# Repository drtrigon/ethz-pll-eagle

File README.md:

## Projekte
### Blattdurchmesser

https://gitlab.ethz.ch/PLL/Blattdurchmesser

https://github.com/drtrigon/ethz-pll-eagle/tree/result/pcb

## Setup

I would like to use features like CI (continous integration) keep a copy/mirror on e.g. github and more.

ETHZ GitLab could (and may be already does) support such features but I do not understand how this works.

Maintaining a copy/mirror (more precise: with 2 remotes overloaded origin) on GitHub also allows
to use GitLab and GitHub together and by that all the nice featurs on GitHub.
See also; https://steveperkins.com/migrating-projects-from-github-to-gitlab/

"Option 2: Overload Origin with Both Remotes (needs one single pull/push only)"; in order to clone
and set this repo up use:
```
$ git clone https://gitlab.ethz.ch/PLL/eagle.git
$ cd eagle
$ git remote set-url --add origin https://github.com/drtrigon/ethz-pll-eagle.git
```
you can check the settings with:
```
$ git remote -v
origin  https://gitlab.ethz.ch/PLL/eagle.git (fetch)
origin  https://gitlab.ethz.ch/PLL/eagle.git (push)
origin  https://github.com/drtrigon/ethz-pll-eagle.git (push)
```

### Enable EDRC.ME for a Repository (for Eagle)
http://www.edrc.me/docs/

### Further Info
https://github.com/drtrigon/eagle

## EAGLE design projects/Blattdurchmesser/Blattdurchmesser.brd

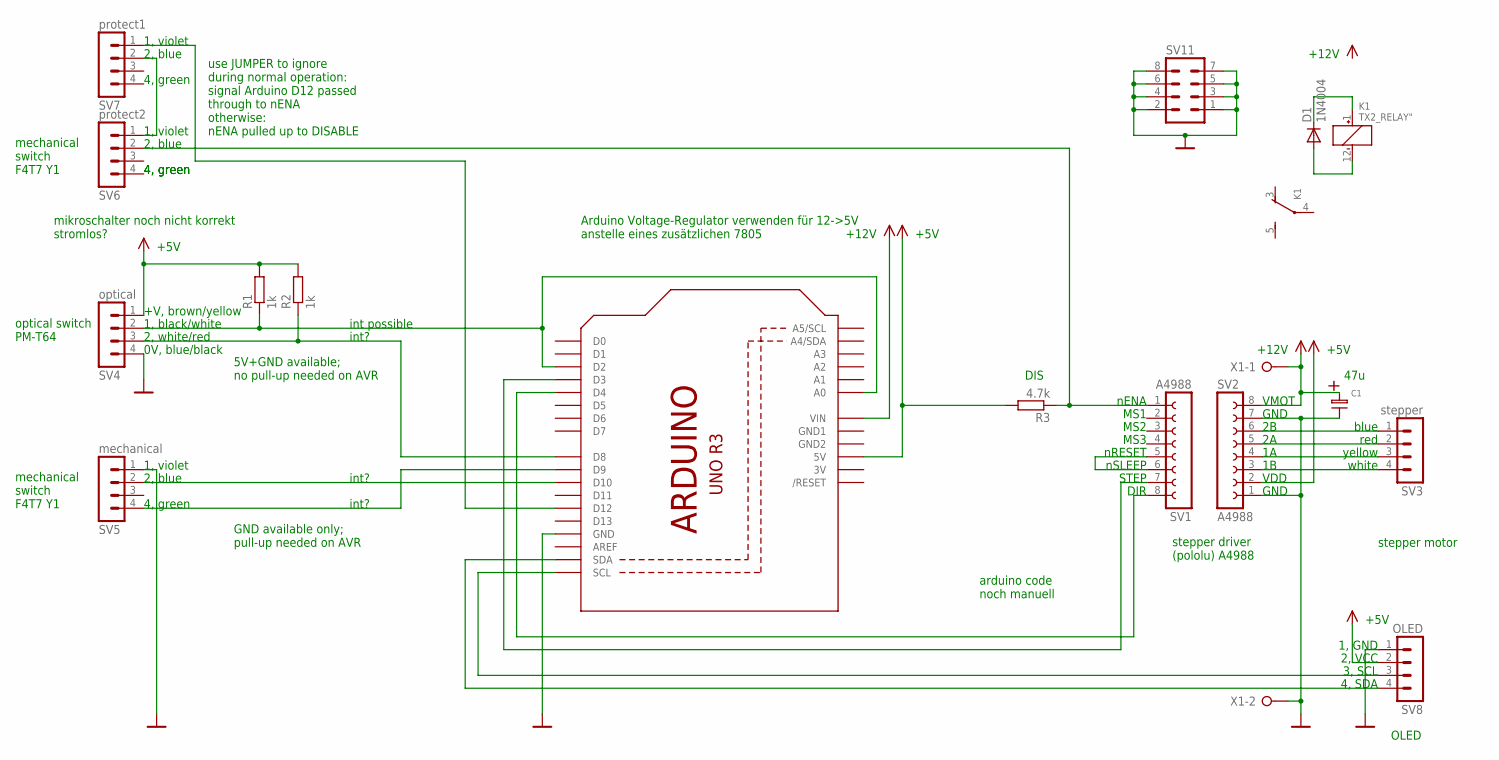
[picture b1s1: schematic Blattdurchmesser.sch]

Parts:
C1: R_ELKO_8.1; R_ELK_8.1
D1: 1N4004; DO41-10
K1: TX2_RELAY"; TX2
Q1: ARDUINOR3-NOIOREF-NOTEXT; ARDUINOR3-NOTEXT-NOIOREF
R1, R2: 1k; 0207/10
R3: 4.7k; 0207/10
SV1, SV2: A4988; FE08
SV3: stepper; MA04-1
SV4: optical; MA04-1
SV5: mechanical; MA04-1
SV6: protect2; MA04-1
SV7: protect1; MA04-1
SV8: OLED; MA04-1
SV11: MA04-2
X1: W237-02P; W237-132

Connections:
3V: Q1.3V
+5V: Q1.5V, R1.2, R2.2, R3.2, SV2.2, SV4.1, SV8.2
+12V: C1.P, Q1.VIN, SV2.8, X1.1
GND: C1.N, Q1.GND, SV2.1, SV2.7, SV4.4, SV5.1, SV8.1, SV11.1, SV11.2, SV11.3, SV11.4, SV11.5, SV11.6, SV11.7, SV11.8, X1.2
GND1: Q1.GND1
GND2: Q1.GND2
unnamed: Q1.D4, SV1.8
unnamed: Q1.D3, SV1.7
unnamed: SV2.6, SV3.1
unnamed: SV2.5, SV3.2
unnamed: SV2.4, SV3.3
unnamed: SV2.3, SV3.4
unnamed: SV1.5, SV1.6
unnamed: D1.A, K1.12 (-)
unnamed: Q1.D8, R2.1, SV4.3
unnamed: SV6.1, SV7.2
unnamed: Q1.D12, SV7.1
unnamed: Q1.D10, SV5.2
unnamed: Q1.D9, SV5.4
unnamed: R3.1, SV1.1, SV6.2
unnamed: Q1.A0, Q1.D2, R1.1, SV4.2
unnamed: D1.C, K1.1 (+)
unnamed: Q1.SCL, SV8.3
unnamed: Q1.SDA, SV8.4

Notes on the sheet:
nENA
MS1
MS2
MS3
nRESET
nSLEEP
STEP
DIR
GND
VDD
VMOT
+12V
+5V
blue
red
yellow
white
DIS
47u
+V, brown/yellow
1, black/white
2, white/red
0V, blue/black
1, violet
2, blue
4, green
5V+GND available; no pull-up needed on AVR
GND available only; pull-up needed on AVR
int possible
int?
optical switch PM-T64
mechanical switch F4T7 Y1
stepper driver (pololu) A4988
stepper motor
use JUMPER to ignore during normal operation: signal Arduino D12 passed through to nENA otherwise: nENA pulled up to DISABLE
arduino code noch manuell
mikroschalter noch nicht korrekt stromlos?
Arduino Voltage-Regulator verwenden für 12->5V anstelle eines zusätzlichen 7805
1, GND
2, VCC

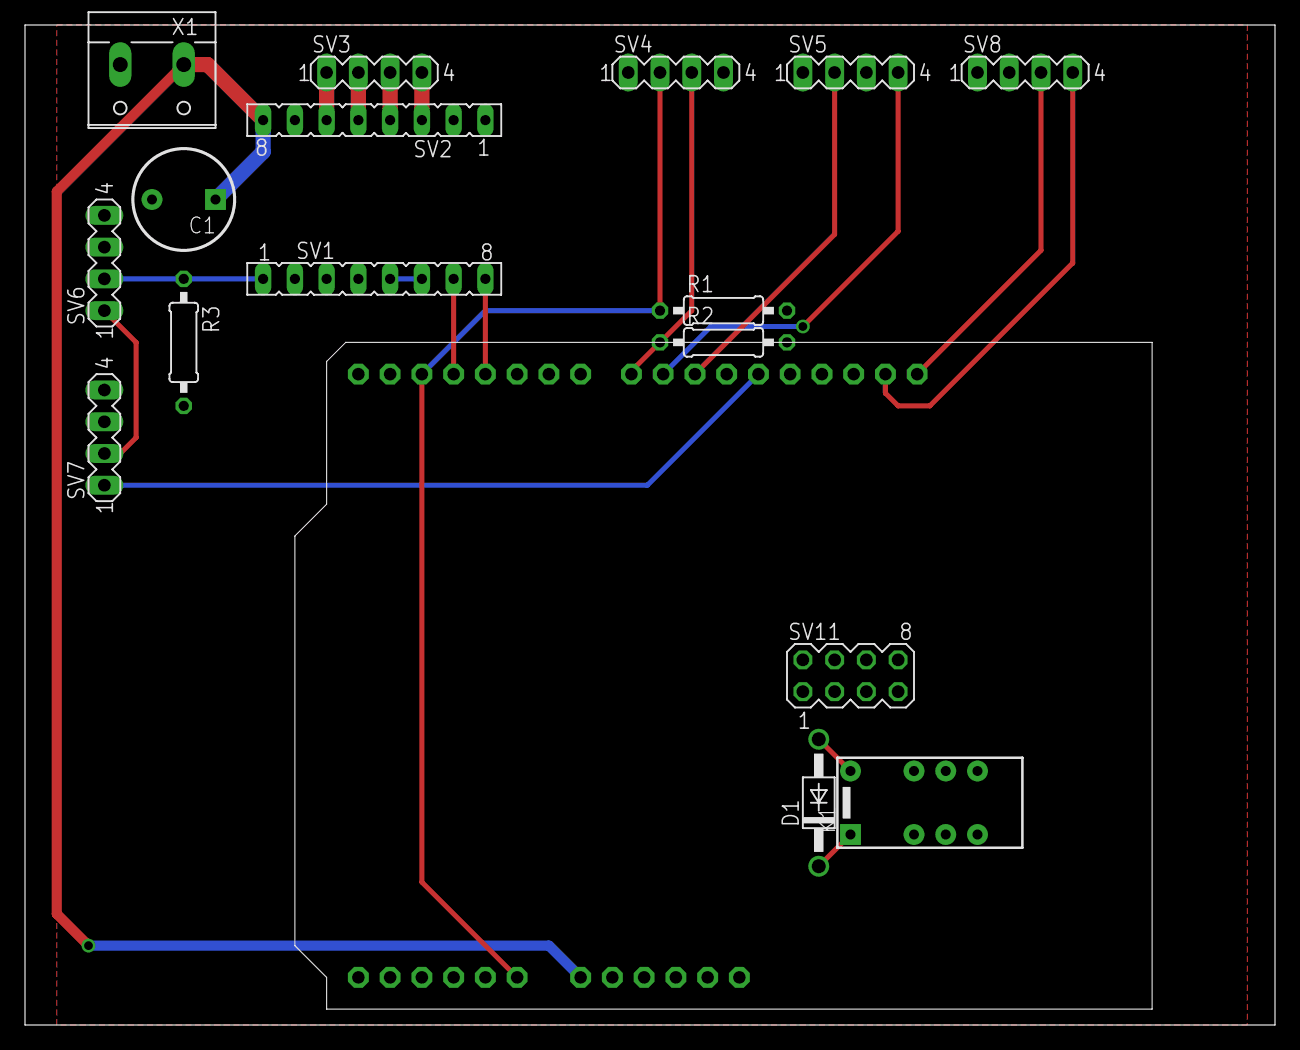
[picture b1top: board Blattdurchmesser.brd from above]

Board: 2 copper layers, 100.0 x 80.0 mm, 17 parts (1 on the bottom side), 21 nets.

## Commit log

2018-03-28 first commit of material
2018-03-28 improvement; * clean-up and compress repo * add note about on how to re-organize the repos
2018-04-04 new features; * add EDRC.me * add eagle-travis * add docu
2018-04-04 improvement; * docu/todo update
2018-04-04 improvement; * eagle first actual schematic * eagle first actual board draft (may need license)
2018-04-04 new feature; * automate gerber file creation
2018-04-04 improvement; * minor changes for travis (which is off) * update eagle lib data
2018-04-04 improvement; * add docu hints
2018-04-04 new feature; * add "makefile" script for gerber through eagle
2018-04-04 new feature; * add repo to github and overload (see Blattdurchmesser) * add docu on how to overload * enable/link to edrc.me for github repo * replace status image with correct one
2018-04-04 improvement; * replace pcb image with correct one
2018-04-04 improvement; * docu rearanged a bit
2018-04-05 improvement; * add edrc docu link
2018-04-05 improvement; * parts on pcb rearranged
2018-04-05 improvement; * fix erdc Dimension Errors
2018-04-06 improvement; * replace arduino part/footprint by one that does not have milling slots * avoid using a relais as it has disadvantages
2018-04-06 improvement; * pcb routed for 1st time
2018-04-06 improvement; * put everything closer to meet space restrictions * add 7805 (+5V) voltage regulator (derive from +12V) * add a wire clamp for +12V power connection
2018-04-06 improvement; * replace 7805 voltage regulator by Arduino on-board one
2018-04-06 improvement; * finish routing (forgot 1 wire)
2018-04-06 bugfix; * set 2 (obsolete) wires to fix edrc errors
2018-04-06 bugfix; * edrc dimension errors
2018-04-06 new feature; * add i2c OLED display
2018-04-06 improvement; * rearranged schematic * rearranged pcb
2018-04-06 improvement; * move stepper power line to top plane * add labels to connectors
2018-04-06 bugfix; * move part of stepper power line to bottom plane again because of restrict conflict
2018-04-13 new feature; * enable eagle-travis stuff * update docu accordingly
2018-04-13 bugfix; * push result to correct repo
2018-04-20 new feature; * add more eagle output
2018-04-20 Travis build 3
